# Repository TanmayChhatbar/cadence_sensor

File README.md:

# BREAKING FLAW - The BMW output current is insufficient for the ESP32
# (WIP) ESP32 Accelerometer-Based Sensor with Wireless Display Integration
## Overview

This project involves the development of a compact, low-power sensor unit using an ESP32 microcontroller integrated with an accelerometer and powered by a 3.7V LiPo cell, which can be charged using solar energy. The sensor unit wirelessly transmits data over BLE. The system is designed for measuring the cadence when riding a bicycle for live telemetry, with low energy consumption and a tiny form factor.

## Features

- ESP32-Based Sensor Unit: Equipped with an accelerometer to capture motion data.
- Power Options: 3.7V LiPo.
- Charging Options: USB or Solar
- Wireless Data Transmission: Utilizes Bluetooth Low Energy (BLE) for communication between the sensor unit and the display unit.
- Low Power Consumption: Optimized for energy efficiency, suitable for long-term operation on minimal power. The device will go into sleep mode in case of inactivity.

## Components

- ESP32-S3-WROOM-1 Microcontroller: The core of the system, handling both sensor data collection and wireless communication.
- ICM-42670-P Accelerometer: Detects and measures acceleration in three axes.
- BQ25570 BMS: For voltage regulation for the circuit and battery charging.

## Setup and Installation

- Hardware Setup
  - Assemble the ESP32 with the accelerometer and choose either the button cell or solar cell for power.
  - Connect to ESP32 with Bluetooth.

- Software Setup
  - Flash the ESP32 with the provided codebase.
  - The sensor unit will continuously monitor the accelerometer data and send it via BLE to the display unit.
  - The display unit will process and visualize the received data.

## Usage

- The sensor unit will send data, and the display unit will show the live accelerometer readings.

## PCB Design

Below is the image of the PCB design, showcasing the layout of the components for the sensor unit.

## Future Improvements

- Integration of additional sensors (e.g., gyroscope).
- Enhanced power management strategies for longer battery life.
- Expansion to support multiple sensor units communicating with a single display.

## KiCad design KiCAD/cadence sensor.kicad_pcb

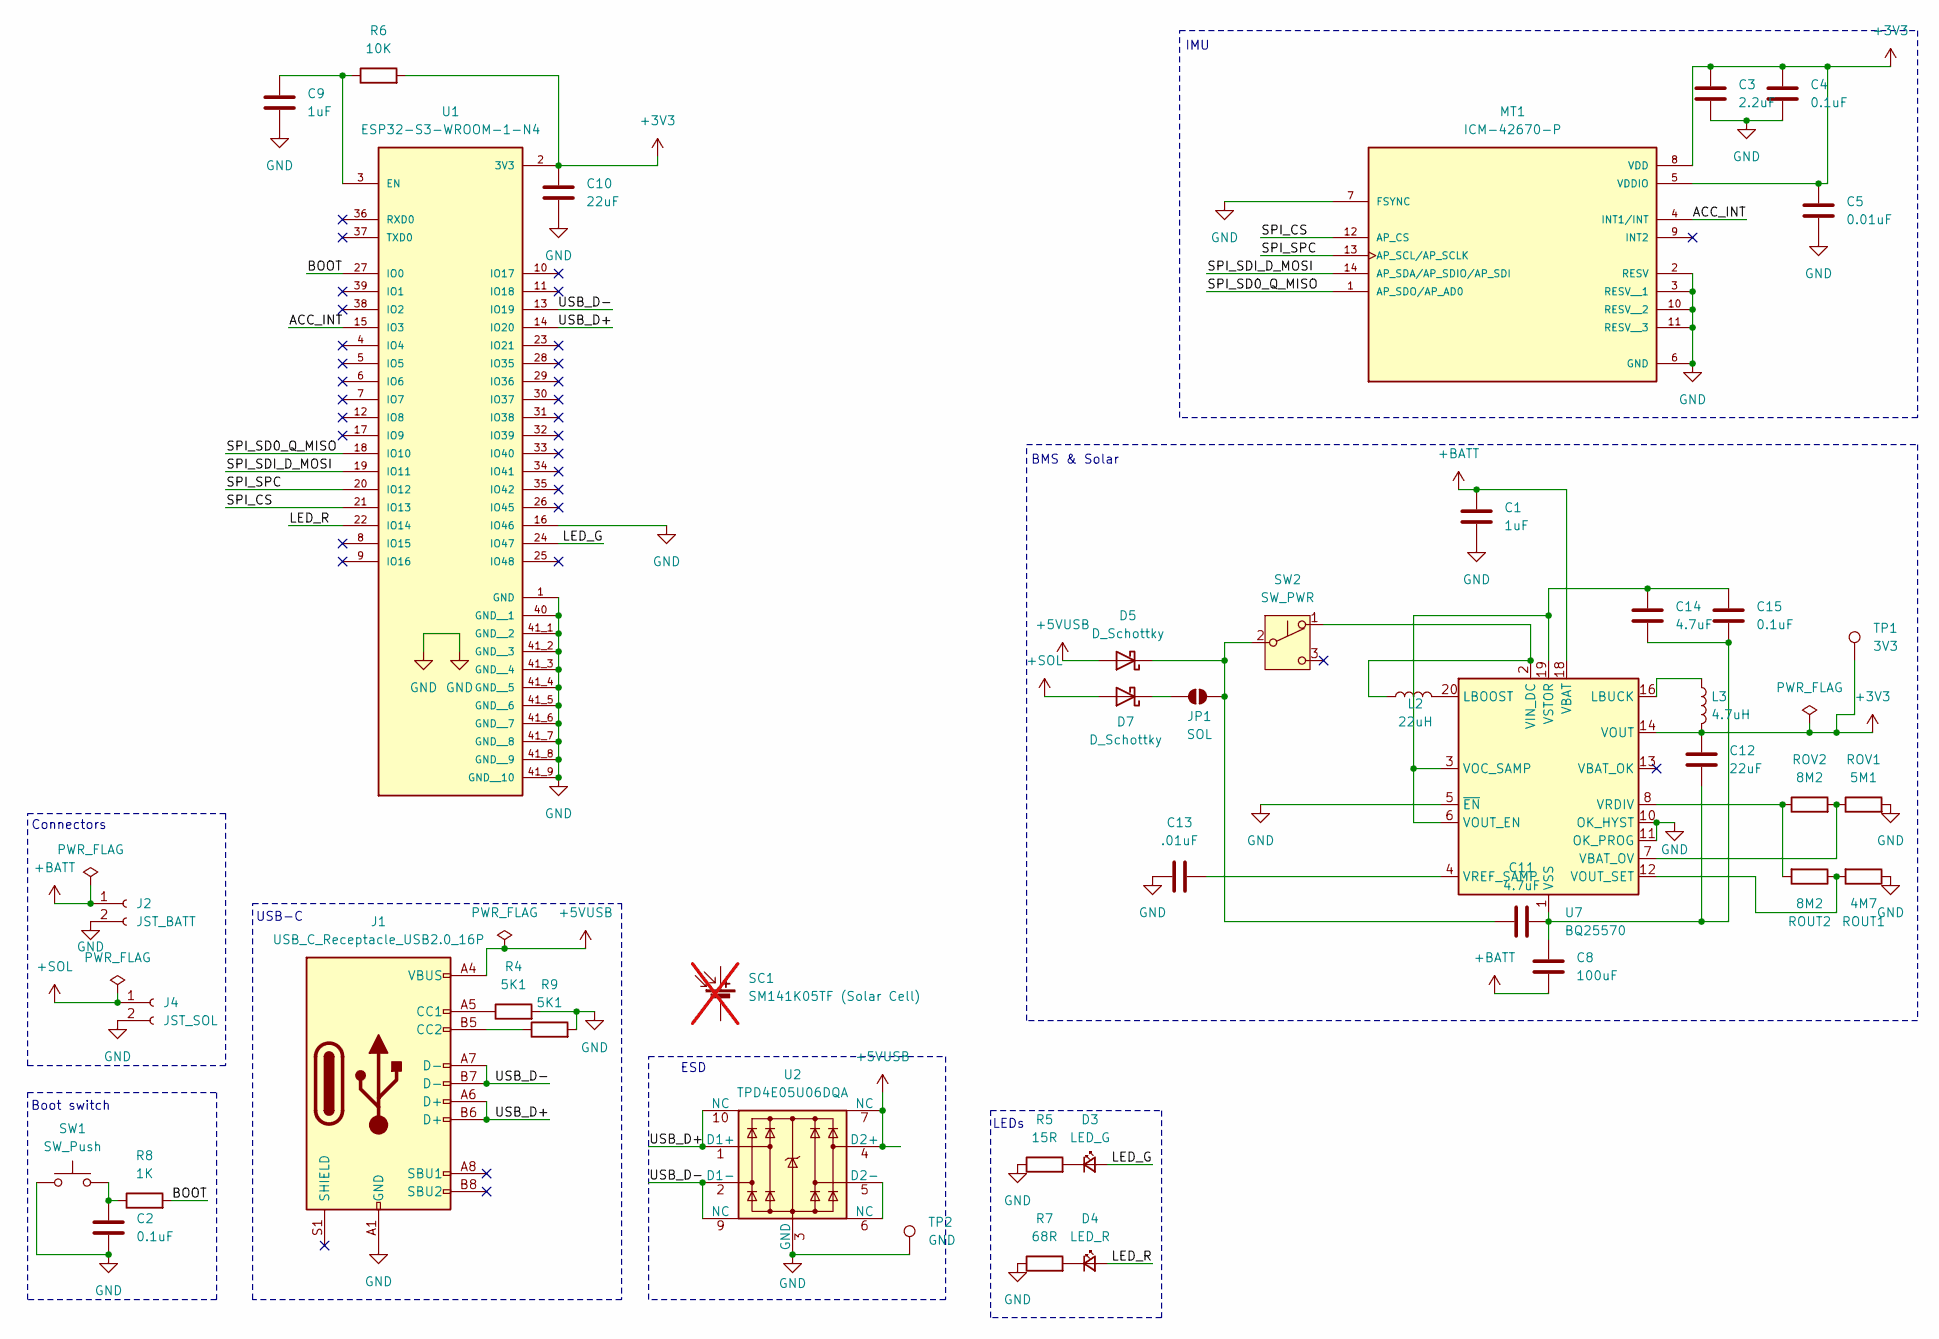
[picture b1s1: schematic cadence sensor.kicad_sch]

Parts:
C1, C9: 1uF; C_1206_3216Metric
C2, C4, C15: 0.1uF; C_1206_3216Metric
C3: 2.2uF; C_1206_3216Metric
C5: 0.01uF; C_1206_3216Metric
C8: 100uF; C_1206_3216Metric
C10, C12: 22uF; C_1206_3216Metric
C11, C14: 4.7uF; C_1206_3216Metric
C13: .01uF; C_1206_3216Metric
D3: LED_G; D_1206_3216Metric
D4: LED_R; D_1206_3216Metric
D5, D7: D_Schottky; D_SOD-123
J1: USB_C_Receptacle_USB2.0_16P; USB_C_Receptacle_GCT_USB4110
J2: JST_BATT; JST_XH_S2B-XH-A-1_1x02_P2.50mm_Horizontal
J4: JST_SOL; JST_XH_S2B-XH-A-1_1x02_P2.50mm_Horizontal
JP1: SOL; SolderJumper-2_P1.3mm_Open_RoundedPad1.0x1.5mm
L2: 22uH; L_1206_3216Metric
L3: 4.7uH; L_1206_3216Metric
MT1: ICM-42670-P; XDCR_ICM-42670-P; PARTREV 1.1
R4, R9: 5K1; R_1206_3216Metric
R5: 15R; R_1206_3216Metric
R6: 10K; R_1206_3216Metric
R7: 68R; R_1206_3216Metric
R8: 1K; R_1206_3216Metric
ROUT1: 4M7; R_1206_3216Metric
ROUT2: 8M2; R_1206_3216Metric
ROV1: 5M1; R_1206_3216Metric
ROV2: 8M2; R_1206_3216Metric
SC1: SM141K05TF (Solar Cell); not fitted
SW1: SW_Push; SW_Push_SPST_NO_Alps_SKRK
SW2: SW_PWR; switch-MSK-12C02-smd
TP1: 3V3; TestPoint_Pad_D2.0mm
TP2: GND; TestPoint_Pad_D2.0mm
U1: ESP32-S3-WROOM-1-N4; XCVR_ESP32-S3-WROOM-1-N4; PARTREV v1.0
U2: TPD4E05U06DQA; USON-10_2.5x1.0mm_P0.5mm
U7: BQ25570; QFN-20-1EP_3.5x3.5mm_P0.5mm_EP2x2mm

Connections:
+3V3: C3.1, C4.1, C5.1, C10.1, C12.2, L3.2, MT1.5 (VDDIO), MT1.8 (VDD), R6.2, TP1.1, U1.2 (3V3), U7.14 (VOUT)
+5VUSB: D5.2 (A), J1.A4 (VBUS), J1.A9 (VBUS), J1.B4 (VBUS), J1.B9 (VBUS), U2.4 (D2+), U2.7 (NC)
+BATT: C1.1, C8.2, J2.1, U7.18 (VBAT)
+SOL: D7.2 (A), J4.1
/ACC_INT: MT1.4 (INT1/INT), U1.15 (IO3)
/BOOT: R8.2, U1.27 (IO0)
/LED_G: D3.2 (A), U1.24 (IO47)
/LED_R: D4.2 (A), U1.22 (IO14)
/SPI_CS: MT1.12 (AP_CS), U1.21 (IO13)
/SPI_SD0_Q_MISO: MT1.1 (AP_SDO/AP_AD0), U1.18 (IO10)
/SPI_SDI_D_MOSI: MT1.14 (AP_SDA/AP_SDIO/AP_SDI), U1.19 (IO11)
/SPI_SPC: MT1.13 (AP_SCL/AP_SCLK), U1.20 (IO12)
/USB_D+: J1.A6 (D+), J1.B6 (D+), U1.14 (IO20), U2.1 (D1+), U2.10 (NC)
/USB_D-: J1.A7 (D-), J1.B7 (D-), U1.13 (IO19), U2.2 (D1-), U2.9 (NC)
GND: C1.2, C2.2, C3.2, C4.2, C5.2, C9.2, C10.2, C13.1, J1.A1 (GND), J1.A12 (GND), J1.B1 (GND), J1.B12 (GND), J2.2, J4.2, MT1.2 (RESV), MT1.3 (RESV__1), MT1.6 (GND), MT1.7 (FSYNC), MT1.10 (RESV__2), MT1.11 (RESV__3), R4.2, R5.1, R7.1, R9.2, ROUT1.1, ROV1.2, SW1.1, TP2.1, U1.1 (GND), U1.16 (IO46), U1.40 (GND__1), U1.41_1 (GND__2), U1.41_2 (GND__3), U1.41_3 (GND__4), U1.41_4 (GND__5), U1.41_5 (GND__6), U1.41_6 (GND__7), U1.41_7 (GND__8), U1.41_8 (GND__9), U1.41_9 (GND__10), U2.3 (GND), U2.8 (GND), U7.5 (~EN), U7.10 (OK_HYST), U7.11 (OK_PROG)
unnamed: C2.1, R8.1, SW1.2
unnamed: C8.1, C11.2, C12.1, C14.1, C15.1, U7.1 (VSS), U7.9 (VSS), U7.15 (VSS), U7.17 (VSS), U7.21 (VSS)
unnamed: D3.1 (K), R5.2
unnamed: D4.1 (K), R7.2
unnamed: C11.1, D5.1 (K), JP1.2 (B), SW2.2 (B)
unnamed: D7.1 (K), JP1.1 (A)
unnamed: J1.A5 (CC1), R4.1
unnamed: J1.B5 (CC2), R9.1
unnamed: L2.1, SW2.1 (A), U7.2 (VIN_DC)
unnamed: C9.1, R6.1, U1.3 (EN)
unnamed: U2.5 (D2-), U2.6 (NC)
unnamed: L2.2, U7.20 (LBOOST)
unnamed: L3.1, U7.16 (LBUCK)
unnamed: ROV1.1, ROV2.2, U7.7 (VBAT_OV)
unnamed: C14.2, C15.2, U7.3 (VOC_SAMP), U7.6 (VOUT_EN), U7.19 (VSTOR)
unnamed: ROUT1.2, ROUT2.1, U7.12 (VOUT_SET)
unnamed: ROUT2.2, ROV2.1, U7.8 (VRDIV)
unnamed: C13.2, U7.4 (VREF_SAMP)

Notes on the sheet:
LEDs
BMS & Solar
Boot switch
ESD
Connectors
IMU
USB-C

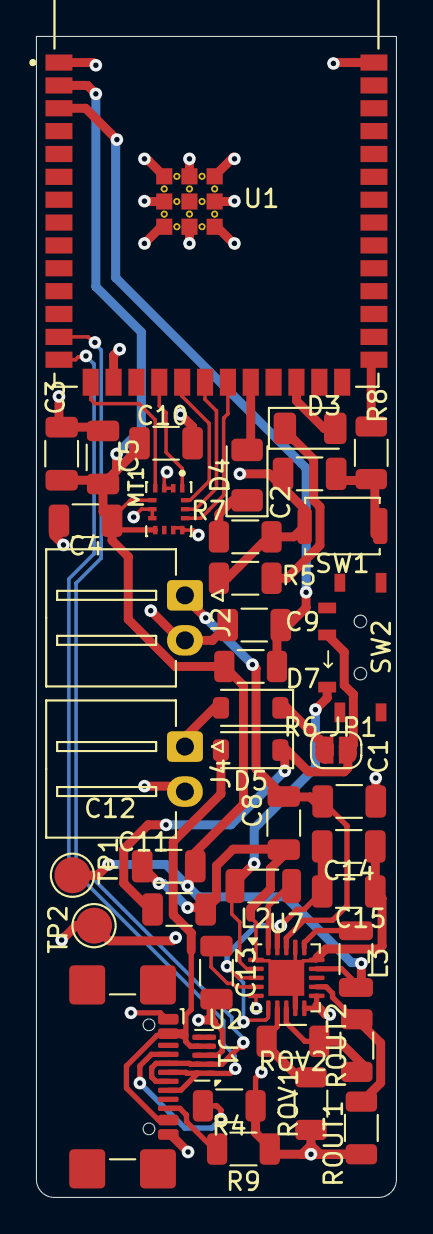
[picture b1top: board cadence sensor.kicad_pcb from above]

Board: 2 copper layers, 20.0 x 64.5 mm, 41 parts (0 on the bottom side), 33 nets.

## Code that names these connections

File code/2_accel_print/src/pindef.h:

#define LED_G GPIO_NUM_47
#define LED_R GPIO_NUM_14

#define SPI_SPC GPIO_NUM_10      // clock
#define SPI_MISO GPIO_NUM_11     // master out slave in
#define SPI_MOSI GPIO_NUM_12     // master in slave out 
#define SPI_CS  GPIO_NUM_13      // chip select

#define ACC_INT GPIO_NUM_3       // accelerometer interrupt

#define BOOT GPIO_NUM_0

#define USB_DP GPIO_NUM_20       // USB_D+
#define USB_DN GPIO_NUM_19       // USB_D-

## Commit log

2024-09-23 add all files
2024-09-23 move idea to readme
2024-09-26 add gitignore
2024-09-26 Update .gitignore to ignore .pio directories
2024-09-26 update gitignore
2024-09-26 added nominal accelerometer. compiled, not tested
2024-09-26 trying own library for ICM42670P
2024-09-26 update platformio config
2024-09-26 KiCAD use local modified of footprint for JST connector
2024-09-26 use photo for readme from media folder
2024-09-26 untrack cache files
2024-09-26 untrack vscode cache
2024-09-26 remove JST custom files
2024-09-26 remove some unnecessary information
2024-09-26 move KiCAD downloads to its folder
2024-09-26 remove KiCAD backup files
2024-09-26 rename pcb image in media folder and its reference in README
2024-09-26 update gitignore for KiCAD files
2024-09-26 update all platformio configs
2024-09-26 ignore reference files
2024-09-26 move printed.zip to releases
2024-09-26 moved excel to misc
2024-09-26 add notes file
2024-09-26 ignore KiCAD lock files while editing
2024-09-26 ignore KiCAD locked files on edit - update
2024-09-27 CAD changes in KiCAD 3d model
2024-09-27 add step file for PCB
2024-09-27 save KiCAD
2024-09-27 utils prettify
2024-09-28 add NX part file
2024-10-07 found issue in PCB design
2024-10-07 add datasheet links
2024-10-31 Update README.md with breaking flaw warning
